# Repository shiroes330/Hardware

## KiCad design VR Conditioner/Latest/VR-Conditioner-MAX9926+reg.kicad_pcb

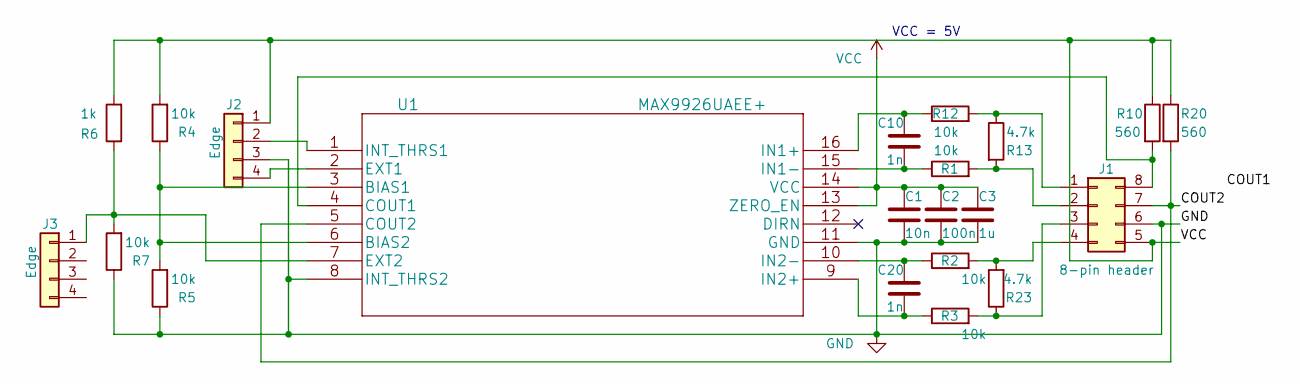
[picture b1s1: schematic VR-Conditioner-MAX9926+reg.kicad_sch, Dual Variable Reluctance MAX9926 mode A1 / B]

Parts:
C1: 10n; C_0805_2012Metric_Pad1.18x1.45mm_HandSolder; MFG Part Num GRM1857U1A103JA44D
C2: 100n; C_0805_2012Metric_Pad1.18x1.45mm_HandSolder; MFG Part Num GCJ188R71C104KA01D
C3: 1u; C_0805_2012Metric_Pad1.18x1.45mm_HandSolder; MFG Part Num GCM188R71C105KA64D
C10, C20: 1n; C_1206_3216Metric_Pad1.33x1.80mm_HandSolder; MFG Part Num GRM1885C1H102JA01D
J1: 8-pin header; DIP-8_W7.62mm
J2, J3: Edge; PinHeader_1x04_P2.54mm_Horizontal
R1, R12: 10k; R_1206_3216Metric_Pad1.30x1.75mm_HandSolder; MFG Part Num RC1206FR-7W10KL
R2, R3: 10k; R_1206_3216Metric; MFG Part Num RC1206FR-7W10KL
R4, R5, R7: 10k; R_1206_3216Metric_Pad1.30x1.75mm_HandSolder
R6: 1k; R_2512_6332Metric_Pad1.40x3.35mm_HandSolder
R10: 560; C_0805_2012Metric_Pad1.18x1.45mm_HandSolder; MFG Part Num CRCW06031K00FKEAHP
R13, R23: 4.7k; R_1206_3216Metric_Pad1.30x1.75mm_HandSolder
R20: 560; R_0805_2012Metric_Pad1.20x1.40mm_HandSolder; MFG Part Num CRCW06031K00FKEAHP
U1: MAX9926UAEE+; MAX9926UAEE&plus_; MFG Part Num MAX9926UAEE+

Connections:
/COUT1: J1.8, R10.2, U1.4 (COUT1)
/COUT2: J1.7, R20.2, U1.5 (COUT2)
GND: C1.2, C2.2, C3.2, J1.6, J2.3, R5.1, R7.1, U1.8 (INT_THRS2), U1.11 (GND)
unnamed: J1.1, R12.2, R13.1
unnamed: J1.2, R1.2, R13.2
unnamed: J1.3, R3.2, R23.1
unnamed: J1.4, R2.2, R23.2
unnamed: J2.2, U1.1 (INT_THRS1)
unnamed: J2.4, U1.2 (EXT1)
unnamed: J3.1, R6.1, R7.2, U1.7 (EXT2)
unnamed: R4.1, R5.2, U1.3 (BIAS1), U1.6 (BIAS2)
unnamed: C10.1, R12.1, U1.16 (IN1+)
unnamed: C10.2, R1.1, U1.15 (IN1-)
unnamed: C20.2, R3.1, U1.9 (IN2+)
unnamed: C20.1, R2.1, U1.10 (IN2-)
VCC: C1.1, C2.1, C3.1, J1.5, J2.1, R4.2, R6.2, R10.1, R20.1, U1.13 (ZERO_EN), U1.14 (VCC)

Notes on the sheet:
VCC = 5V

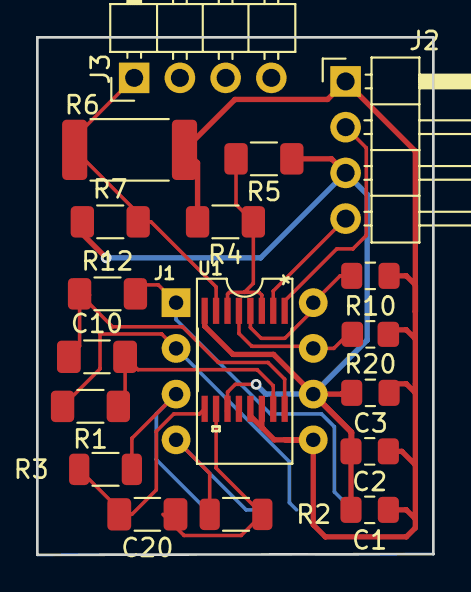
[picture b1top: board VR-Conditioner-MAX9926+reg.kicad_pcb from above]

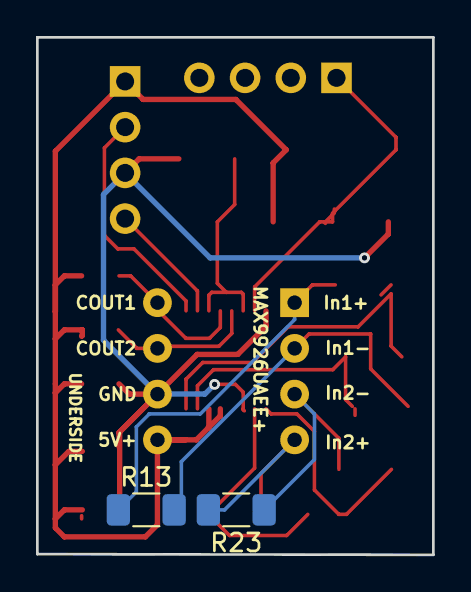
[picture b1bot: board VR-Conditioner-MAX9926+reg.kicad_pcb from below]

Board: 2 copper layers, 22.0 x 28.8 mm, 21 parts (2 on the bottom side), 16 nets.

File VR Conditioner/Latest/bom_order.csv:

"Reference","Value","Datasheet","Footprint","Qty","DNP"
"C1","10n","~","Capacitor_SMD:C_0805_2012Metric_Pad1.18x1.45mm_HandSolder","1",""
"C2","100n","~","Capacitor_SMD:C_0805_2012Metric_Pad1.18x1.45mm_HandSolder","1",""
"C3","1u","~","Capacitor_SMD:C_0805_2012Metric_Pad1.18x1.45mm_HandSolder","1",""
"C10","1n","~","Capacitor_SMD:C_1206_3216Metric_Pad1.33x1.80mm_HandSolder","1",""
"C20","1n","~","Capacitor_SMD:C_1206_3216Metric_Pad1.33x1.80mm_HandSolder","1",""
"J1","8-pin header","~","Package_DIP:DIP-8_W7.62mm","1",""
"R1","10k","~","Resistor_SMD:R_1206_3216Metric_Pad1.30x1.75mm_HandSolder","1",""
"R2","10k","~","Resistor_SMD:R_1206_3216Metric","1",""
"R3","10k","~","Resistor_SMD:R_1206_3216Metric","1",""
"R4","10k","~","Resistor_SMD:R_1206_3216Metric_Pad1.30x1.75mm_HandSolder","1",""
"R5","10k","~","Resistor_SMD:R_1206_3216Metric_Pad1.30x1.75mm_HandSolder","1",""
"R6","1k","~","Resistor_SMD:R_2512_6332Metric_Pad1.40x3.35mm_HandSolder","1",""
"R7","10k","~","Resistor_SMD:R_1206_3216Metric_Pad1.30x1.75mm_HandSolder","1",""
"R10","560","~","Capacitor_SMD:C_0805_2012Metric_Pad1.18x1.45mm_HandSolder","1",""
"R12","10k","~","Resistor_SMD:R_1206_3216Metric_Pad1.30x1.75mm_HandSolder","1",""
"R13","4.7k","~","Resistor_SMD:R_1206_3216Metric_Pad1.30x1.75mm_HandSolder","1",""
"R20","560","~","Resistor_SMD:R_0805_2012Metric_Pad1.20x1.40mm_HandSolder","1",""
"R23","4.7k","~","Resistor_SMD:R_1206_3216Metric_Pad1.30x1.75mm_HandSolder","1",""
"U1","MAX9926UAEE+","https://datasheet.octopart.com/MAX9926UAEE%2B-Maxim-Integrat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","MAX9926UAEE+:MAX9926UAEE&plus_","1",""

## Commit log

2024-07-30 Update original vr conditioner

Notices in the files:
VR Conditioner/Latest/VR-Conditioner-MAX9926+reg.kicad_pcb:
(c)2021 Phill Rogers @ TechColab.co.je
parts and their libraries:
Copyright 2016 Accelerated Designs. All rights reserved.
